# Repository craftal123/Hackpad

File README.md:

# Hackpad
Its my first blueprint ever for the hackclub and i am so excited!

This is the finished 3D model:

Why i did it in the first place?:
I decided i wanted to make the hackpad because i always loved robotics and electronics, as i started making youtube and using my pc for editing i really wanted a streamer deck but it is too expensive for me, i saw about hackclub in a video but a few days ago i saw an instagram rell about the hackpad!

My case:

BOM:
  4x Cherry MX Switches
  2x SK6812 MINI Leds
  1x XIAO RP2040
  4x Blank DSA Keycaps
  4x M3x16 Bolt
  4x M3 Heatset
  1x EC11 Rotary encoder

Schematic:

PCB:

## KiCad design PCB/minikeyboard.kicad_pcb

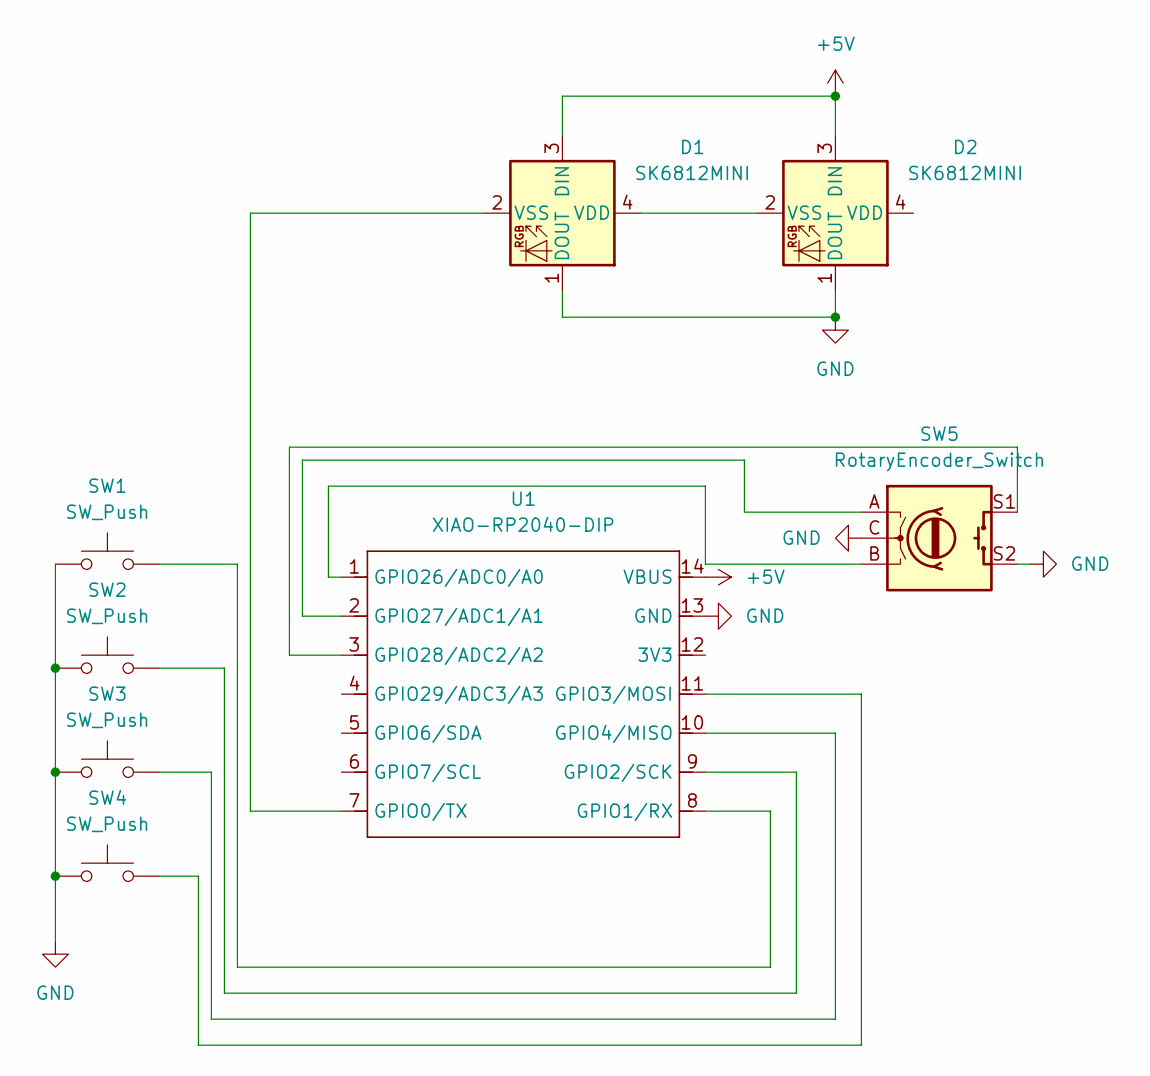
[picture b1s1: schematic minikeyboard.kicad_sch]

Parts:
D1, D2: SK6812MINI; MX_SK6812MINI-E_REV
SW1, SW2, SW3, SW4: SW_Push; SW_Cherry_MX_1.00u_PCB
SW5: RotaryEncoder_Switch; RotaryEncoder_Alps_EC11E-Switch_Vertical_H20mm
U1: XIAO-RP2040-DIP

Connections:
+5V: D1.3 (DIN), D2.3 (DIN), U1.14 (VBUS)
GND: D1.1 (DOUT), D2.1 (DOUT), SW1.1, SW2.1, SW3.1, SW4.1, SW5.C, SW5.S2, U1.13 (GND)
unnamed: D1.4 (VDD), D2.2 (VSS)
unnamed: D1.2 (VSS), U1.7 (GPIO0/TX)
unnamed: SW1.2, U1.8 (GPIO1/RX)
unnamed: SW2.2, U1.9 (GPIO2/SCK)
unnamed: SW4.2, U1.11 (GPIO3/MOSI)
unnamed: SW3.2, U1.10 (GPIO4/MISO)
unnamed: SW5.B, U1.1 (GPIO26/ADC0/A0)
unnamed: SW5.A, U1.2 (GPIO27/ADC1/A1)
unnamed: SW5.S1, U1.3 (GPIO28/ADC2/A2)

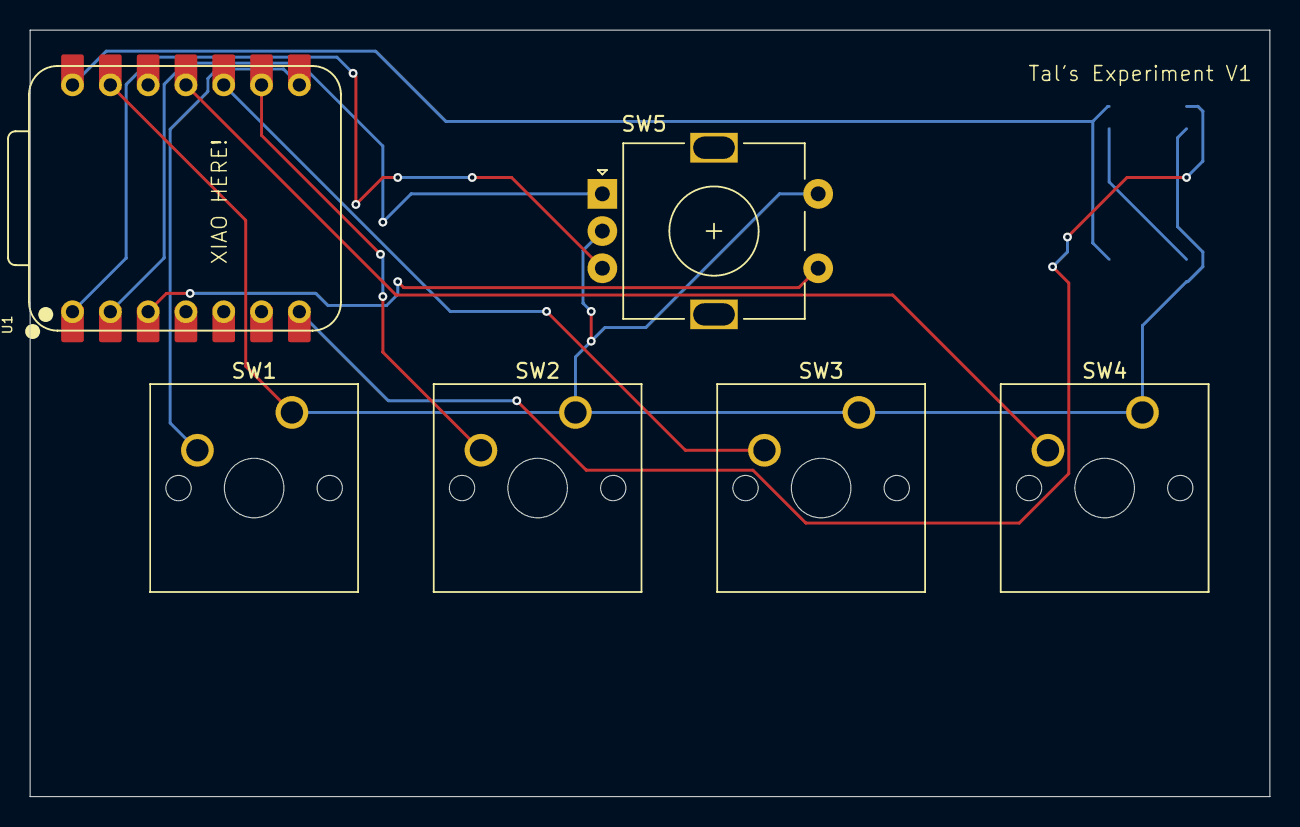
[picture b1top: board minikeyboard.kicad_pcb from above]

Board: 2 copper layers, 83.3 x 51.5 mm, 8 parts (0 on the bottom side), 11 nets.

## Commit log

2026-01-19 README.md
2026-01-19 First version
2026-01-23 Change the code from QMK to KMK and added an encoder
